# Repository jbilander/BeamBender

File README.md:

# BeamBender
An open source flicker fixer PCB for Amiga 1200 and 500 to be fitted under the floppy drive.

WORK IN PROGRESS, NOT FINISHED!!!

***

Rev. 1B
<br />

<br />

***

Rev. 1A
<br />

<br />

<br />

<br />

<br />

<br />

<br />

***

BOM Rev. 1B
---------
Designator  | Name/Value   | Package | Notes
-|-|-|-|
U1 | Voltage Regulator 3.3V, <br /> LM1117-3.3 or <br /> AMS1117-3.3 | SOT-223 | 3.3V 1A Low Drop-Out (LDO) Voltage regulator. https://www.aliexpress.com/item/32869037691.html
U2 | Gowin FPGA GW1NR-UV9LQ144PC6/I5 | LQFP-144 | FPGA - Field Programmable Gate Array, 8640 LE, 121 I/O, Embedded 64Mbit 16-bit PSRAM <br /> [GW1NR-UV9LQ144PC6/I5](https://www.mouser.com/ProductDetail/192-1NRUV9LQ144PC6I5)
U3 | SiI9022A | QFN-72-1EP_10x10mm_P0.5mm_EP4.7x4.7mm | 165 MHz High Performance HDMI Transmitter [SII9022ACNU](https://www.mouser.com/ProductDetail/842-SII9022ACNU)
U4 | Voltage Regulator 1.8V, <br /> MCP1702T-1802E/CB | SOT-23 | 1.8V Low Drop-Out (LDO) Voltage regulator. [MCP1702T1802E-CB](https://www.mouser.com/ProductDetail/579-MCP1702T1802E-CB)
U5 | Audio A/D Converter AK5720VT | TSSOP-16 | ADC IC 2ch 24bit 96K. [AK5720VT](https://www.mouser.se/ProductDetail/412-AK5720VT)
U6 | Voltage Regulator 1.2V, <br /> MCP1702T-1202E/CB | SOT-23 | 1.2V Low Drop-Out (LDO) Voltage regulator. [MCP1702T1202E-CB](https://eu.mouser.com/ProductDetail/579-MCP1702T1202E-CB)
X1 | Abracon ASE-27.000MHZ-L-R-T | XTAL OSC SMD 3.2 mm x 2.5 mm | Standard Clock Oscillator XO 27MHZ CMOS SMD [ASE-27.000MHZ-L-R-T](https://www.mouser.com/ProductDetail/815-ASE-27.000-LR-T)
X2 | Abracon ASFL1-24.576MHZ-EC-T | XTAL OSC SMD 5.0 mm x 3.2 mm | Standard Clock Oscillators 24.576 MHZ 15PF 3.3V [ASFL1-24.576MHZ-EC-T](https://www.mouser.com/ProductDetail/815-ASFL1-24.5-EC-T)
X3 | Standard Clock Oscillator 50 MHz, 3.3V LVCMOS | XTAL OSC SMD 7 mm x 5 mm | e.g. [FN5000109](https://www.mouser.com/ProductDetail/729-FN5000109) or [LH736050](https://www.mouser.com/ProductDetail/972-LH736050.000000I)
J1 | FFC & FPC Connectors .5 FPC VT ZIF Type-A | 40 Position FPC connector, Pitch 0.5 mm | [TE Connectivity 4-1734742-0](https://www.mouser.com/ProductDetail/571-4-1734742-0)
J2 | HDMI 1.4 Receptacle Connector 19 Position Surface Mount, Right Angle TH | HDMI Receptacle | [Amphenol 10029449-111RLF](https://www.mouser.com/ProductDetail/649-10029449-111RLF)
J3 | Phone Connectors 3.5 mm, Stereo | 3 Position Through Hole | [Kycon STX-3501-3N](https://www.mouser.com/ProductDetail/806-STX-3501-3N)
J4 | VCC/GND Phoenix Contact 2pin 2.54mm pitch | Fixed Terminal Blocks 2P 2.54mm 90DEG | VIN +5V <br /> Be careful with orientation, check polarity BEFORE connecting anything here. You can take +5V/GND from internal floppy pin-header on Amiga motherboard.<br />[1725656](https://www.mouser.com/ProductDetail/651-1725656) or [Aliexpress](https://www.aliexpress.com/item/1005001677869988.html)
D1-D3 | ESD Suppressors / TVS Diodes | U-DFN2510-10 | [D5V0F4U10LP-7](https://www.mouser.com/ProductDetail/621-D5V0F4U10LP-7)
D4 | ESD Suppressor / TVS Diode 1 Ch | SOD-723-2 | [SP1003-01DTG](https://www.mouser.com/ProductDetail/576-SP1003-01DTG) Optional ESD protection for VCC.
D5 | Diode - General Purpose | 0805 | e.g. [TS4148RBG](https://www.mouser.com/ProductDetail/821-TS4148RBG) Diode in RC-debounce (R5, C34) circuit for BT1 (Button 1).
L1-L4 | Ferrite Bead 600ohms 100MHz .5A Monolithic | 0805 | e.g. [HZ0805E601R-10](https://www.mouser.com/ProductDetail/875-HZ0805E601R-10)
C1-C13 | Capacitor 10uF | 1206 |
C14 | Capacitor 0.47uF | 1206 | e.g. [UMK316B7474KL-T](https://www.mouser.com/ProductDetail/963-UMK316B7474KL-T)
C15, C16 | Capacitor 0.1uF | 1206 |
C17 | Polarized Capacitor 100uF | CP_Elec_6.3x7.7 | e.g. [Wurth SMD WCAP-AS5H 100uF](https://www.mouser.com/ProductDetail/710-865230245004)
C18, C19 | Polarized Capacitor 22uF | CP_Elec_5x5.8 | e.g. [Wurth SMD WCAP-AS5H 22uF](https://www.mouser.com/ProductDetail/710-865230342002)
C20-C22 | Capacitor 1uF | 0805 |
C23-C43 | Capacitor 0.1uF = 100nF | 0805 |
C44-C47 | Capacitor 0.1uF = 100nF | 0603 |
C48-C53 | Capacitor 0.01uF = 10nF | 0603 |
R1-R3 | 1k Ω | 0805 |
R4, R5 | 10k Ω | 0805 |
R6 | 0-9 Ω or solder blob| 0805 | e.g. [CR0805-J/-000ELF](https://www.mouser.com/ProductDetail/652-CR0805-J-000ELF)
R7-R14 | 33 Ω | 0603 | e.g. [CR0603-FX-33R0ELF](https://www.mouser.com/ProductDetail/652-CR0603FX-33R0ELF)
R15, R16 | 2k Ω | 0603 | e.g. [CR0603-FX-2001ELF](https://www.mouser.com/ProductDetail/652-CR0603-FX-2001LF)
R17 | 4.3k Ω, 1% tolerance | 0603 | e.g. [CR0603-FX-4301ELF](https://www.mouser.com/ProductDetail/652-CR0603FX-4301ELF) The recommended value is 4.3k Ω ±1% with internal source termination enabled and 5.1k Ω ±1% without internal source termination. 
R18-R20 | 4.7k Ω | 0603 | 
R21 | 10k Ω | 0603 |
RN1, RN2 | CAY16A-4701F4LF RES ARRAY 4 Resistors 4.7k Ω | 1206 | [CAY16A-4701F4LF](https://eu.mouser.com/ProductDetail/652-CAY16A-4701F4LF)

***

[![CC BY-SA 4.0][cc-by-sa-shield]][cc-by-sa]

This work is licensed under a
[Creative Commons Attribution-ShareAlike 4.0 International License][cc-by-sa].

[![CC BY-SA 4.0][cc-by-sa-image]][cc-by-sa]

[cc-by-sa]: http://creativecommons.org/licenses/by-sa/4.0/
[cc-by-sa-image]: https://licensebuttons.net/l/by-sa/4.0/88x31.png
[cc-by-sa-shield]: https://img.shields.io/badge/License-CC%20BY--SA%204.0-lightgrey.svg

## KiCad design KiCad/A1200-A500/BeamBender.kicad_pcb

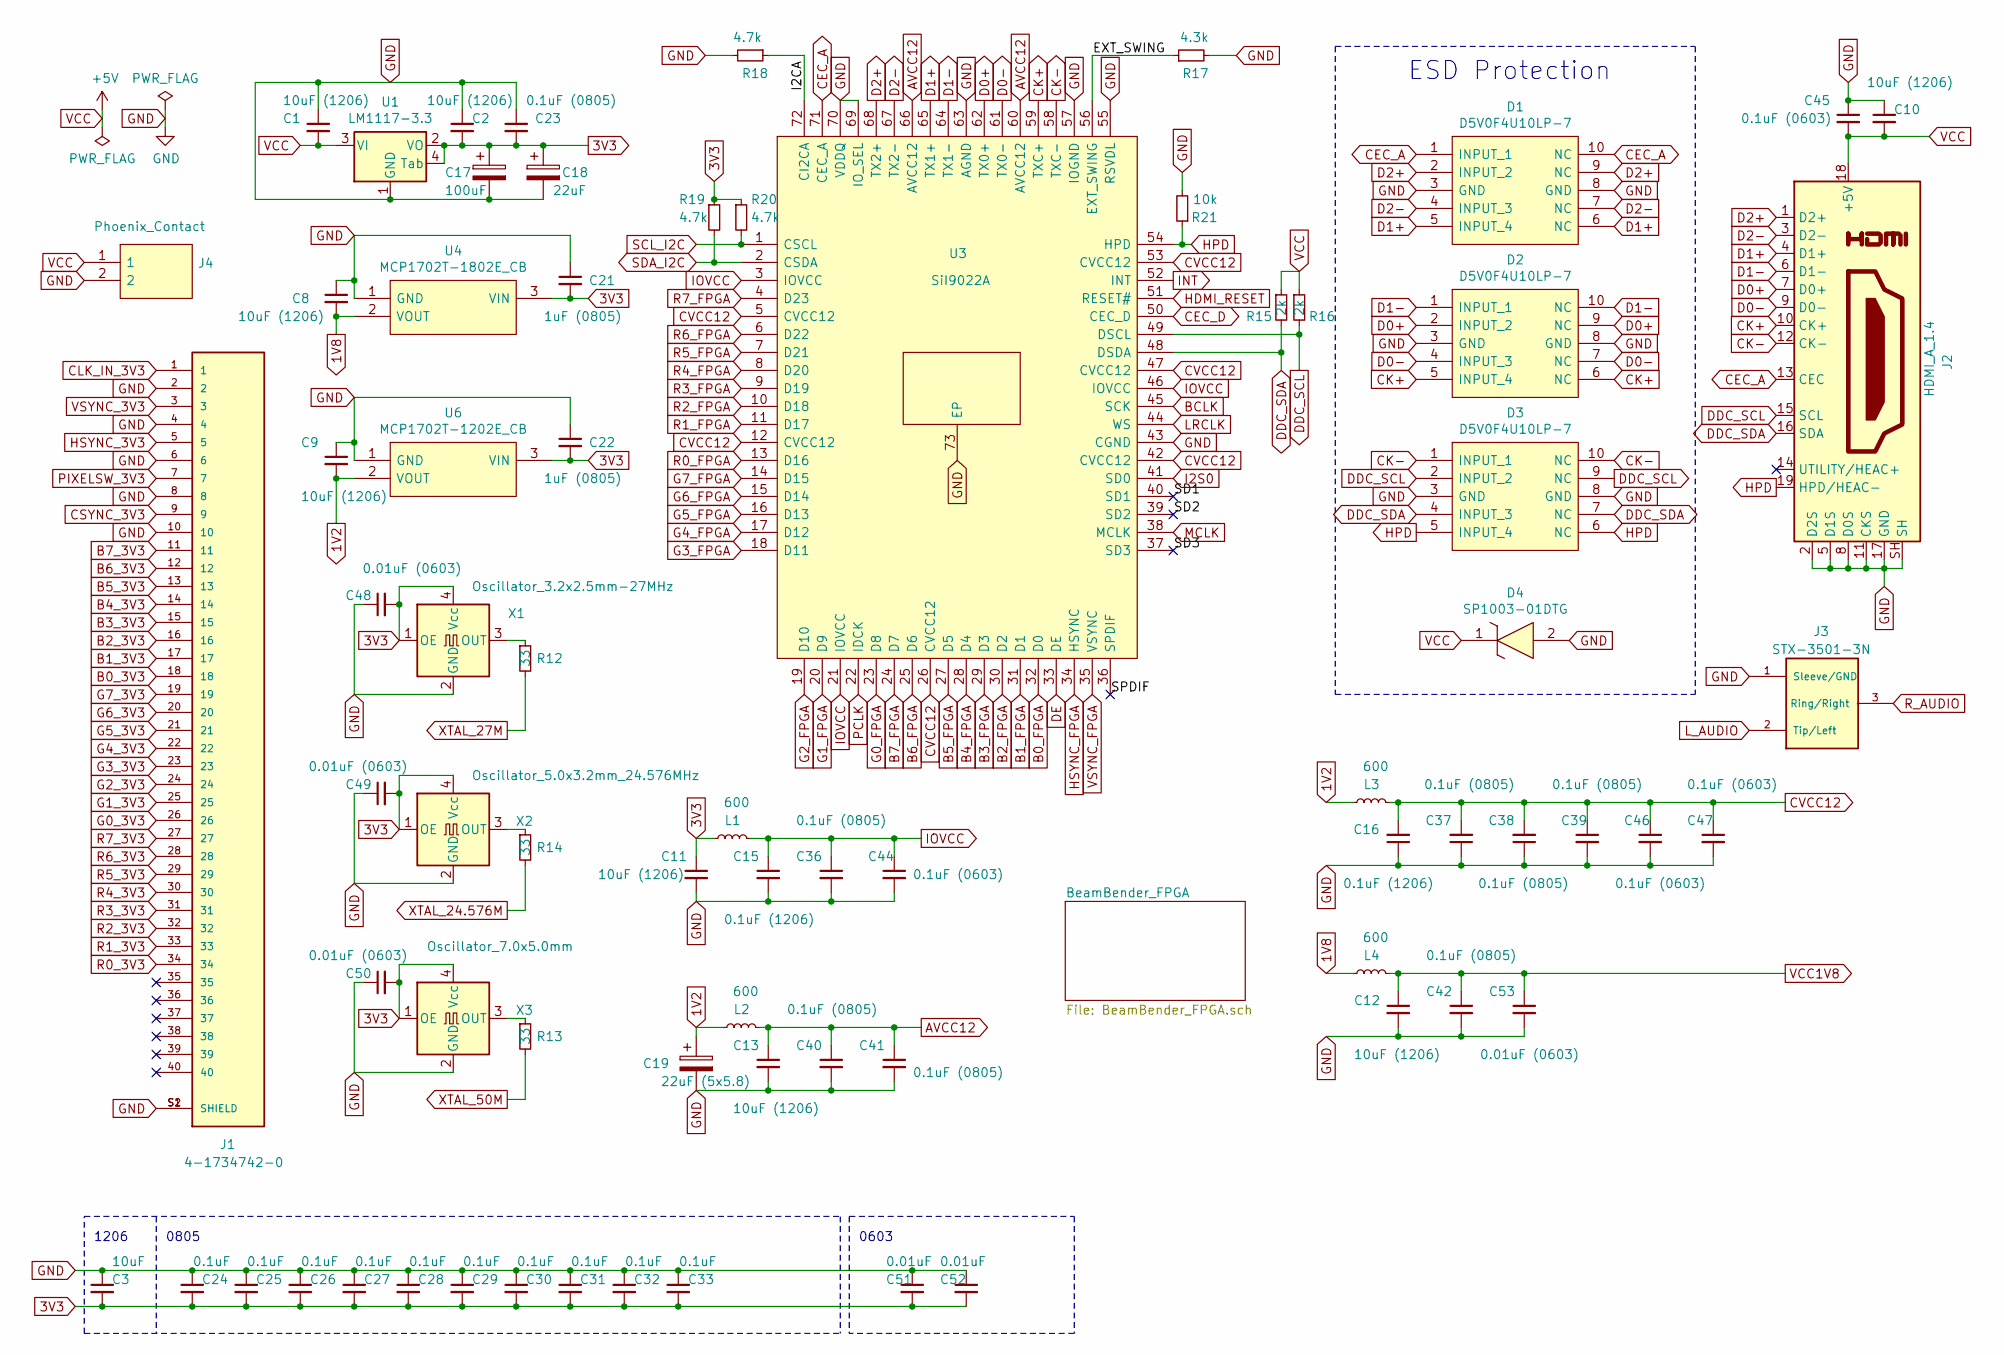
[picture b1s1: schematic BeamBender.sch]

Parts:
C1, C2: 10uF (1206); C_1206_3216Metric_Pad1.42x1.75mm_HandSolder
C3: 10uF; C_1206_3216Metric_Pad1.33x1.80mm_HandSolder
C8, C9, C10, C11, C12, C13: 10uF (1206); C_1206_3216Metric_Pad1.33x1.80mm_HandSolder
C15, C16: 0.1uF (1206); C_1206_3216Metric_Pad1.33x1.80mm_HandSolder
C17: 100uF; CP_Elec_6.3x7.7
C18: 22uF; CP_Elec_5x5.8
C19: 22uF (5x5.8); CP_Elec_5x5.8
C21, C22: 1uF (0805); C_0805_2012Metric_Pad1.18x1.45mm_HandSolder
C23: 0.1uF (0805); C_0805_2012Metric_Pad1.15x1.40mm_HandSolder
C24, C25, C26, C27, C28, C29, C30, C31, C32, C33: 0.1uF; C_0805_2012Metric_Pad1.18x1.45mm_HandSolder
C36, C37, C38, C39, C40, C41, C42: 0.1uF (0805); C_0805_2012Metric_Pad1.18x1.45mm_HandSolder
C44, C45, C46, C47: 0.1uF (0603); C_0603_1608Metric_Pad1.08x0.95mm_HandSolder
C48, C49, C50, C53: 0.01uF (0603); C_0603_1608Metric_Pad1.08x0.95mm_HandSolder
C51, C52: 0.01uF; C_0603_1608Metric_Pad1.08x0.95mm_HandSolder
D1, D2, D3: D5V0F4U10LP-7; Diodes_UDFN-10_1.0x2.5mm_P0.5mm_HandSolder
D4: SP1003-01DTG; D_0603_1608Metric
J1: 4-1734742-0; TE_4-1734742-0; PARTREV P
J2: HDMI_A_1.4; HDMI-10029449-111RLF
J3: STX-3501-3N; STX35013N
J4: Phoenix_Contact
L1, L2, L3, L4: 600; L_0805_2012Metric_Pad1.15x1.40mm_HandSolder
R12, R13, R14: 33; R_0603_1608Metric_Pad0.98x0.95mm_HandSolder
R15, R16: 2k; R_0603_1608Metric_Pad0.98x0.95mm_HandSolder
R17: 4.3k; R_0603_1608Metric_Pad0.98x0.95mm_HandSolder
R18, R19, R20: 4.7k; R_0603_1608Metric_Pad0.98x0.95mm_HandSolder
R21: 10k; R_0603_1608Metric_Pad0.98x0.95mm_HandSolder
U1: LM1117-3.3; SOT-223
U3: SiI9022A; QFN-72-1EP_10x10mm_P0.5mm_EP6x6mm_ThermalVias_HandSolder
U4: MCP1702T-1802E_CB; SOT-23_Handsoldering
U6: MCP1702T-1202E_CB; SOT-23_Handsoldering
X1: Oscillator_3.2x2.5mm-27MHz; Oscillator_SMD_SeikoEpson_SG8002CE-4Pin_3.2x2.5mm
X2: Oscillator_5.0x3.2mm_24.576MHz; Oscillator_SMD_TXC_7C-4Pin_5.0x3.2mm_HandSoldering
X3: Oscillator_7.0x5.0mm; Oscillator_SMD_SeikoEpson_SG8002CA-4Pin_7.0x5.0mm_HandSolde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

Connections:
1V2: C9.2, C19.1, L2.1, L3.1, U6.2 (VOUT)
1V8: C8.2, L4.1, U4.2 (VOUT)
3V3: C2.2, C3.2, C11.1, C17.1, C18.1, C21.2, C22.2, C23.2, C24.2, C25.2, C26.2, C27.2, C28.2, C29.2, C30.2, C31.2, C32.2, C33.2, C48.2, C49.2, C50.2, C51.2, C52.2, L1.1, R19.1, R20.1, U1.2 (VO), U1.4 (Tab), U4.3 (VIN), U6.3 (VIN), X1.1 (OE), X1.4 (Vcc), X2.1 (OE), X2.4 (Vcc), X3.1 (OE), X3.4 (Vcc); also elsewhere on the board
/EXT_SWING: R17.1, U3.56 (EXT_SWING)
/I2CA: R18.1, U3.72 (CI2CA)
/SD1: U3.40 (SD1)
/SD2: U3.39 (SD2)
/SD3: U3.37 (SD3)
/SPDIF: U3.36 (SPDIF)
AVCC12: C13.1, C40.1, C41.1, L2.2, U3.60 (AVCC12), U3.66 (AVCC12)
B0_3V3: J1.18; also elsewhere on the board
B0_FPGA: U3.32 (D0); also elsewhere on the board
B1_3V3: J1.17; also elsewhere on the board
B1_FPGA: U3.31 (D1); also elsewhere on the board
B2_3V3: J1.16; also elsewhere on the board
B2_FPGA: U3.30 (D2); also elsewhere on the board
B3_3V3: J1.15; also elsewhere on the board
B3_FPGA: U3.29 (D3); also elsewhere on the board
B4_3V3: J1.14; also elsewhere on the board
B4_FPGA: U3.28 (D4); also elsewhere on the board
B5_3V3: J1.13; also elsewhere on the board
B5_FPGA: U3.27 (D5); also elsewhere on the board
B6_3V3: J1.12; also elsewhere on the board
B6_FPGA: U3.25 (D6); also elsewhere on the board
B7_3V3: J1.11; also elsewhere on the board
B7_FPGA: U3.24 (D7); also elsewhere on the board
BCLK: U3.45 (SCK); also elsewhere on the board
CEC_A: D1.1 (INPUT_1), D1.10 (NC), J2.13 (CEC), U3.71 (CEC_A)
CEC_D: U3.50 (CEC_D); also elsewhere on the board
CK+: D2.5 (INPUT_4), D2.6 (NC), J2.10 (CK+), U3.59 (TXC+)
CK-: D3.1 (INPUT_1), D3.10 (NC), J2.12 (CK-), U3.58 (TXC-)
CLK_IN_3V3: J1.1; also elsewhere on the board
CSYNC_3V3: J1.9; also elsewhere on the board
CVCC12: C16.2, C37.2, C38.2, C39.1, C46.1, C47.1, L3.2, U3.5 (CVCC12), U3.12 (CVCC12), U3.26 (CVCC12), U3.42 (CVCC12), U3.47 (CVCC12), U3.53 (CVCC12)
D0+: D2.2 (INPUT_2), D2.9 (NC), J2.7 (D0+), U3.62 (TX0+)
D0-: D2.4 (INPUT_3), D2.7 (NC), J2.9 (D0-), U3.61 (TX0-)
D1+: D1.5 (INPUT_4), D1.6 (NC), J2.4 (D1+), U3.65 (TX1+)
D1-: D2.1 (INPUT_1), D2.10 (NC), J2.6 (D1-), U3.64 (TX1-)
D2+: D1.2 (INPUT_2), D1.9 (NC), J2.1 (D2+), U3.68 (TX2+)
D2-: D1.4 (INPUT_3), D1.7 (NC), J2.3 (D2-), U3.67 (TX2-)
DDC_SCL: D3.2 (INPUT_2), D3.9 (NC), J2.15 (SCL), R16.2, U3.49 (DSCL)
DDC_SDA: D3.4 (INPUT_3), D3.7 (NC), J2.16 (SDA), R15.2, U3.48 (DSDA)
DE: U3.33 (DE); also elsewhere on the board
G0_3V3: J1.26; also elsewhere on the board
G0_FPGA: U3.23 (D8); also elsewhere on the board
G1_3V3: J1.25; also elsewhere on the board
G1_FPGA: U3.20 (D9); also elsewhere on the board
G2_3V3: J1.24; also elsewhere on the board
G2_FPGA: U3.19 (D10); also elsewhere on the board
G3_3V3: J1.23; also elsewhere on the board
G3_FPGA: U3.18 (D11); also elsewhere on the board
G4_3V3: J1.22; also elsewhere on the board
G4_FPGA: U3.17 (D12); also elsewhere on the board
G5_3V3: J1.21; also elsewhere on the board
G5_FPGA: U3.16 (D13); also elsewhere on the board
G6_3V3: J1.20; also elsewhere on the board
G6_FPGA: U3.15 (D14); also elsewhere on the board
G7_3V3: J1.19; also elsewhere on the board
G7_FPGA: U3.14 (D15); also elsewhere on the board
GND: C1.1, C2.1, C3.1, C8.1, C9.1, C10.1, C11.2, C12.2, C13.2, C15.2, C16.1, C17.2, C18.2, C19.2, C21.1, C22.1, C23.1, C24.1, C25.1, C26.1, C27.1, C28.1, C29.1, C30.1, C31.1, C32.1, C33.1, C36.2, C37.1, C38.1, C39.2, C40.2, C41.2, C42.2, C44.2, C45.1, C46.2, C47.2, C48.1, C49.1, C50.1, C51.1, C52.1, C53.2, D1.3 (GND), D1.8 (GND), D2.3 (GND), D2.8 (GND), D3.3 (GND), D3.8 (GND), D4.2, J1.2, J1.4, J1.6, J1.8, J1.10, J1.S1 (SHIELD), J1.S2 (SHIELD), J2.2 (D2S), J2.5 (D1S), J2.8 (D0S), J2.11 (CKS), J2.17 (GND), J2.SH, J3.1 (Sleeve/GND), J4.2, R17.2, R18.2, R21.2, U1.1 (GND), U3.43 (CGND), U3.55 (RSVDL), U3.57 (IOGND), U3.63 (AGND), U3.69 (IO_SEL), U3.70 (VDDQ), U3.73 (EP), U4.1 (GND), U6.1 (GND), X1.2 (GND), X2.2 (GND), X3.2 (GND); also elsewhere on the board
HDMI_RESET: U3.51 (RESET#); also elsewhere on the board
HPD: D3.5 (INPUT_4), D3.6 (NC), J2.19 (HPD/HEAC-), R21.1, U3.54 (HPD)
HSYNC_3V3: J1.5; also elsewhere on the board
HSYNC_FPGA: U3.34 (HSYNC); also elsewhere on the board
I2S0: U3.41 (SD0); also elsewhere on the board
INT: U3.52 (INT); also elsewhere on the board
IOVCC: C15.1, C36.1, C44.1, L1.2, U3.3 (IOVCC), U3.21 (IOVCC), U3.46 (IOVCC)
LRCLK: U3.44 (WS); also elsewhere on the board
L_AUDIO: J3.2 (Tip/Left); also elsewhere on the board
MCLK: U3.38 (MCLK); also elsewhere on the board
unnamed: R12.1, X1.3 (OUT)
unnamed: R13.1, X3.3 (OUT)
unnamed: R14.1, X2.3 (OUT)
PCLK: U3.22 (IDCK); also elsewhere on the board
PIXELSW_3V3: J1.7; also elsewhere on the board
R0_3V3: J1.34; also elsewhere on the board
R0_FPGA: U3.13 (D16); also elsewhere on the board
R1_3V3: J1.33; also elsewhere on the board
R1_FPGA: U3.11 (D17); also elsewhere on the board
R2_3V3: J1.32; also elsewhere on the board
R2_FPGA: U3.10 (D18); also elsewhere on the board
R3_3V3: J1.31; also elsewhere on the board
R3_FPGA: U3.9 (D19); also elsewhere on the board
R4_3V3: J1.30; also elsewhere on the board
R4_FPGA: U3.8 (D20); also elsewhere on the board
R5_3V3: J1.29; also elsewhere on the board
R5_FPGA: U3.7 (D21); also elsewhere on the board
R6_3V3: J1.28; also elsewhere on the board
R6_FPGA: U3.6 (D22); also elsewhere on the board
R7_3V3: J1.27; also elsewhere on the board
R7_FPGA: U3.4 (D23); also elsewhere on the board
R_AUDIO: J3.3 (Ring/Right); also elsewhere on the board
SCL_I2C: R20.2, U3.1 (CSCL); also elsewhere on the board
SDA_I2C: R19.2, U3.2 (CSDA); also elsewhere on the board
VCC: C1.2, C10.2, C45.2, D4.1, J2.18 (+5V), J4.1, R15.1, R16.1, U1.3 (VI); also elsewhere on the board
VCC1V8: C12.1, C42.1, C53.1, L4.2; also elsewhere on the board
VSYNC_3V3: J1.3; also elsewhere on the board
VSYNC_FPGA: U3.35 (VSYNC); also elsewhere on the board
XTAL_24.576M: R14.2; also elsewhere on the board
XTAL_27M: R12.2; also elsewhere on the board
XTAL_50M: R13.2; also elsewhere on the board

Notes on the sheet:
ESD Protection
0805
0603
1206

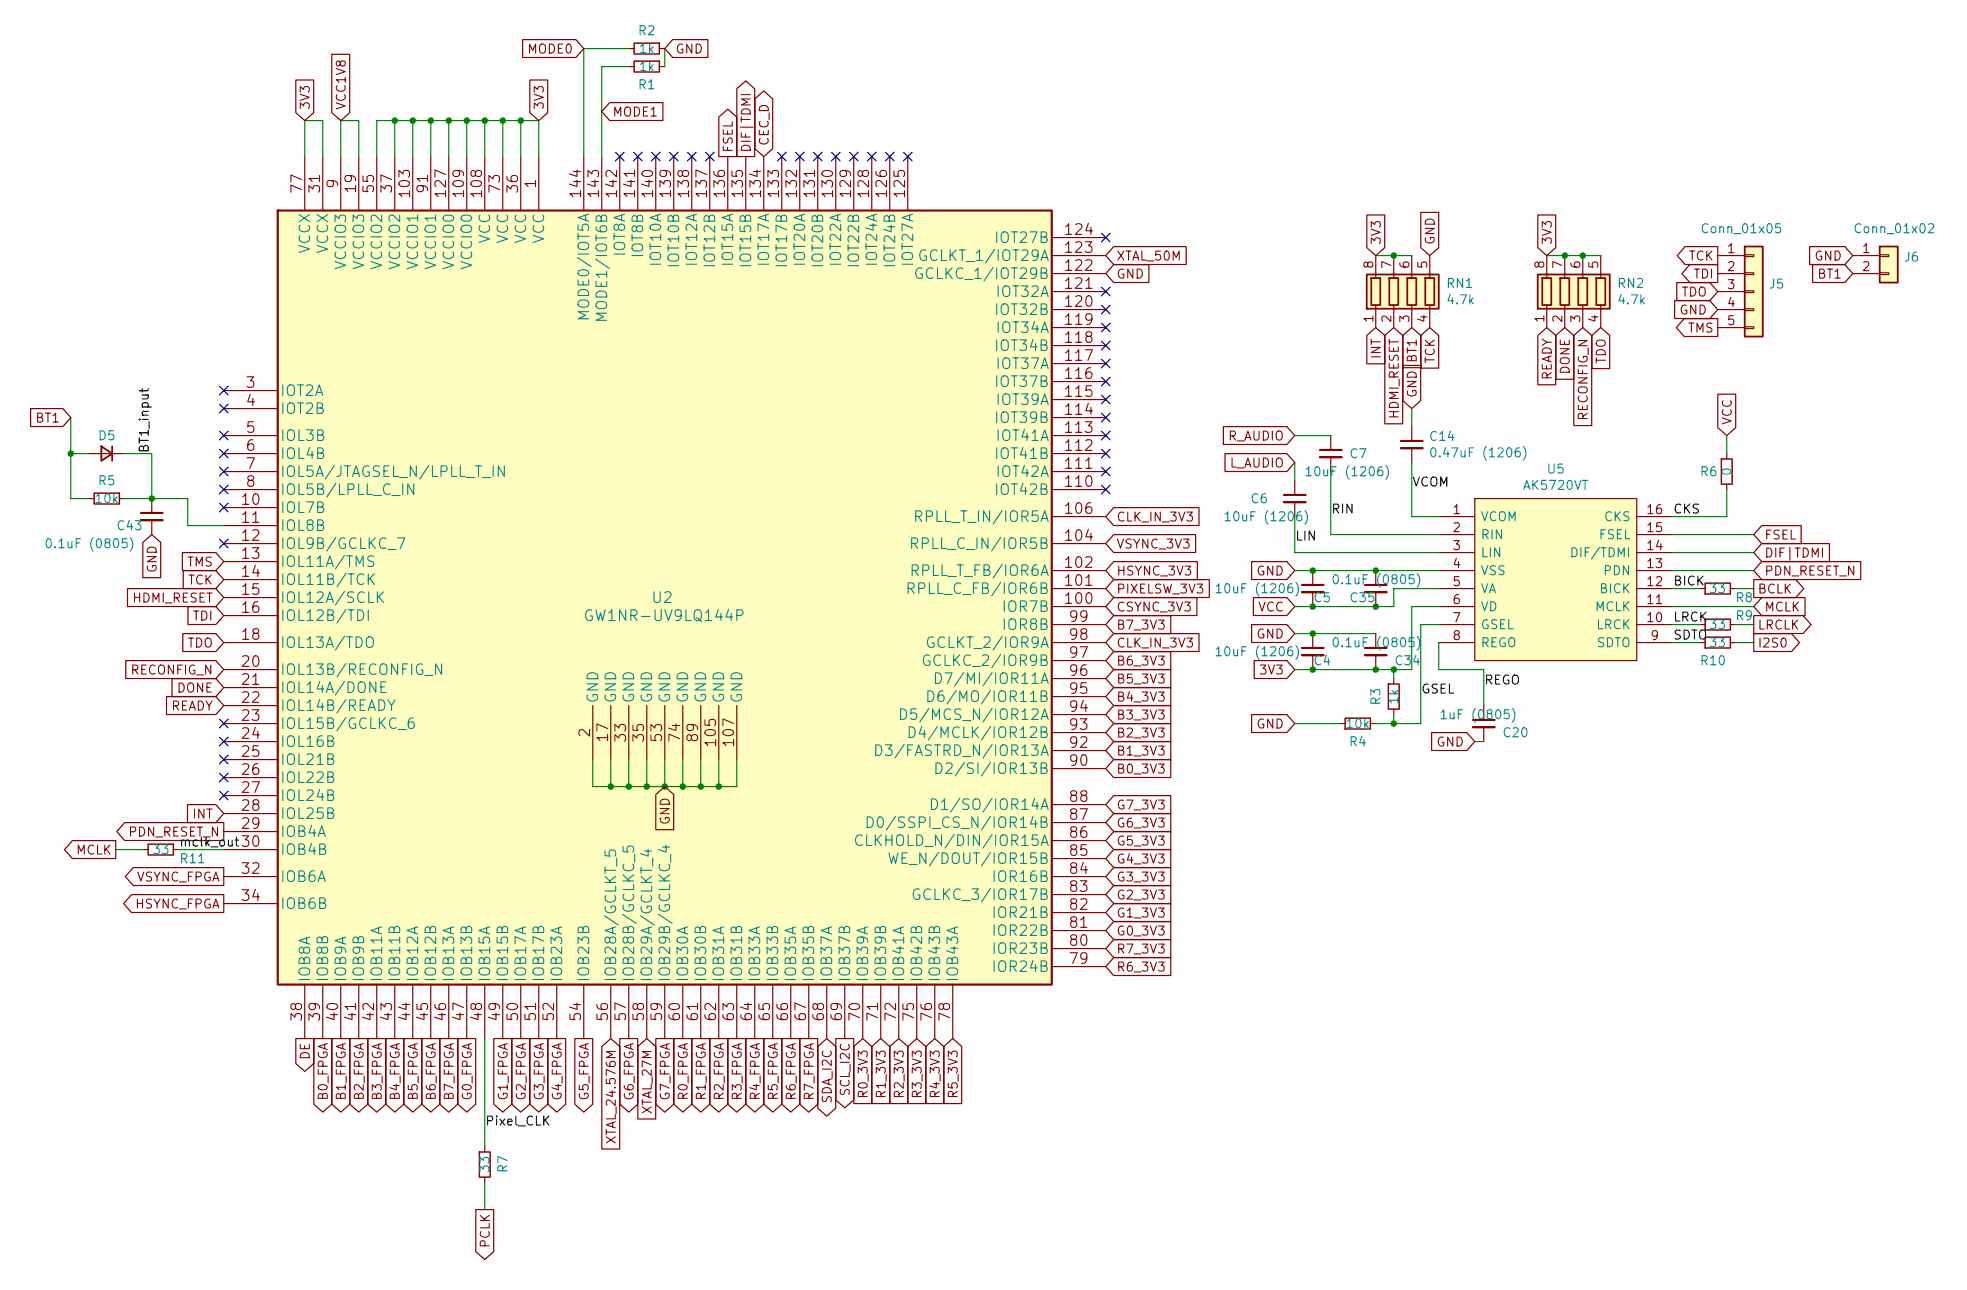
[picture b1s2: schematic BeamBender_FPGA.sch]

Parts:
C4, C5, C6, C7: 10uF (1206); C_1206_3216Metric_Pad1.33x1.80mm_HandSolder
C14: 0.47uF (1206); C_1206_3216Metric_Pad1.33x1.80mm_HandSolder
C20: 1uF (0805); C_0805_2012Metric_Pad1.18x1.45mm_HandSolder
C34, C35, C43: 0.1uF (0805); C_0805_2012Metric_Pad1.18x1.45mm_HandSolder
D5: D_Small; D_0805_2012Metric_Pad1.15x1.40mm_HandSolder
J5: Conn_01x05; PinHeader_1x05_P2.54mm_Vertical
J6: Conn_01x02; PinHeader_1x02_P2.54mm_Vertical
R1, R2, R3: 1k; R_0805_2012Metric_Pad1.20x1.40mm_HandSolder
R4, R5: 10k; R_0805_2012Metric_Pad1.20x1.40mm_HandSolder
R6: 0; R_0805_2012Metric_Pad1.20x1.40mm_HandSolder
R7, R8, R9, R10, R11: 33; R_0603_1608Metric_Pad0.98x0.95mm_HandSolder
RN1, RN2: 4.7k; RESCAF80P320X160X60-8N
U2: GW1NR-UV9LQ144P; LQFP-144_20x20mm_P0.5mm
U5: AK5720VT; TSSOP-16_4.4x5mm_P0.65mm

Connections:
3V3: C4.2, C34.2, R3.1, RN1.6 (R3.2), RN1.7 (R2.2), RN1.8 (R1.2), RN2.5 (R4.2), RN2.6 (R3.2), RN2.7 (R2.2), RN2.8 (R1.2), U2.1 (VCC), U2.31 (VCCX), U2.36 (VCC), U2.37 (VCCIO2), U2.55 (VCCIO2), U2.73 (VCC), U2.77 (VCCX), U2.91 (VCCIO1), U2.103 (VCCIO1), U2.108 (VCC), U2.109 (VCCIO0), U2.127 (VCCIO0), U5.6 (VD); also elsewhere on the board
/BeamBender_FPGA/BICK: R8.1, U5.12 (BICK)
/BeamBender_FPGA/BT1_input: C43.1, D5.1 (K), R5.1, U2.11 (IOL8B)
/BeamBender_FPGA/CKS: R6.2, U5.16 (CKS)
/BeamBender_FPGA/GSEL: R3.2, R4.2, U5.7 (GSEL)
/BeamBender_FPGA/LIN: C6.2, U5.3 (LIN)
/BeamBender_FPGA/LRCK: R9.1, U5.10 (LRCK)
/BeamBender_FPGA/Pixel_CLK: R7.1, U2.48 (IOB15A)
/BeamBender_FPGA/REGO: C20.1, U5.8 (REGO)
/BeamBender_FPGA/RIN: C7.2, U5.2 (RIN)
/BeamBender_FPGA/SDTO: R10.1, U5.9 (SDTO)
/BeamBender_FPGA/VCOM: C14.2, U5.1 (VCOM)
/BeamBender_FPGA/mclk_out: R11.1, U2.30 (IOB4B)
B0_3V3: U2.90 (D2/SI/IOR13B); also elsewhere on the board
B0_FPGA: U2.39 (IOB8B); also elsewhere on the board
B1_3V3: U2.92 (D3/FASTRD_N/IOR13A); also elsewhere on the board
B1_FPGA: U2.40 (IOB9A); also elsewhere on the board
B2_3V3: U2.93 (D4/MCLK/IOR12B); also elsewhere on the board
B2_FPGA: U2.41 (IOB9B); also elsewhere on the board
B3_3V3: U2.94 (D5/MCS_N/IOR12A); also elsewhere on the board
B3_FPGA: U2.42 (IOB11A); also elsewhere on the board
B4_3V3: U2.95 (D6/MO/IOR11B); also elsewhere on the board
B4_FPGA: U2.43 (IOB11B); also elsewhere on the board
B5_3V3: U2.96 (D7/MI/IOR11A); also elsewhere on the board
B5_FPGA: U2.44 (IOB12A); also elsewhere on the board
B6_3V3: U2.97 (GCLKC_2/IOR9B); also elsewhere on the board
B6_FPGA: U2.45 (IOB12B); also elsewhere on the board
B7_3V3: U2.99 (IOR8B); also elsewhere on the board
B7_FPGA: U2.46 (IOB13A); also elsewhere on the board
BCLK: R8.2; also elsewhere on the board
BT1: D5.2 (A), J6.2, R5.2, RN1.3 (R3.1)
CEC_D: U2.134 (IOT17A); also elsewhere on the board
CLK_IN_3V3: U2.98 (GCLKT_2/IOR9A), U2.106 (RPLL_T_IN/IOR5A); also elsewhere on the board
CSYNC_3V3: U2.100 (IOR7B); also elsewhere on the board
DE: U2.38 (IOB8A); also elsewhere on the board
DIF|TDMI: U2.135 (IOT15B), U5.14 (DIF/TDMI)
DONE: RN2.2 (R2.1), U2.21 (IOL14A/DONE)
FSEL: U2.136 (IOT15A), U5.15 (FSEL)
G0_3V3: U2.81 (IOR22B); also elsewhere on the board
G0_FPGA: U2.47 (IOB13B); also elsewhere on the board
G1_3V3: U2.82 (IOR21B); also elsewhere on the board
G1_FPGA: U2.49 (IOB15B); also elsewhere on the board
G2_3V3: U2.83 (GCLKC_3/IOR17B); also elsewhere on the board
G2_FPGA: U2.50 (IOB17A); also elsewhere on the board
G3_3V3: U2.84 (IOR16B); also elsewhere on the board
G3_FPGA: U2.51 (IOB17B); also elsewhere on the board
G4_3V3: U2.85 (WE_N/DOUT/IOR15B); also elsewhere on the board
G4_FPGA: U2.52 (IOB23A); also elsewhere on the board
G5_3V3: U2.86 (CLKHOLD_N/DIN/IOR15A); also elsewhere on the board
G5_FPGA: U2.54 (IOB23B); also elsewhere on the board
G6_3V3: U2.87 (D0/SSPI_CS_N/IOR14B); also elsewhere on the board
G6_FPGA: U2.57 (IOB28B/GCLKC_5); also elsewhere on the board
G7_3V3: U2.88 (D1/SO/IOR14A); also elsewhere on the board
G7_FPGA: U2.59 (IOB29B/GCLKC_4); also elsewhere on the board
GND: C4.1, C5.1, C14.1, C20.2, C34.1, C35.1, C43.2, J5.4, J6.1, R1.1, R2.1, R4.1, RN1.5 (R4.2), U2.2 (GND), U2.17 (GND), U2.33 (GND), U2.35 (GND), U2.53 (GND), U2.74 (GND), U2.89 (GND), U2.105 (GND), U2.107 (GND), U2.122 (GCLKC_1/IOT29B), U5.4 (VSS); also elsewhere on the board
HDMI_RESET: RN1.2 (R2.1), U2.15 (IOL12A/SCLK); also elsewhere on the board
HSYNC_3V3: U2.102 (RPLL_T_FB/IOR6A); also elsewhere on the board
HSYNC_FPGA: U2.34 (IOB6B); also elsewhere on the board
I2S0: R10.2; also elsewhere on the board
INT: RN1.1 (R1.1), U2.28 (IOL25B); also elsewhere on the board
LRCLK: R9.2; also elsewhere on the board
L_AUDIO: C6.1; also elsewhere on the board
MCLK: R11.2, U5.11 (MCLK); also elsewhere on the board
MODE0: R2.2, U2.144 (MODE0/IOT5A)
MODE1: R1.2, U2.143 (MODE1/IOT6B)
PCLK: R7.2; also elsewhere on the board
PDN_RESET_N: U2.29 (IOB4A), U5.13 (PDN)
PIXELSW_3V3: U2.101 (RPLL_C_FB/IOR6B); also elsewhere on the board
R0_3V3: U2.70 (IOB39A); also elsewhere on the board
R0_FPGA: U2.60 (IOB30A); also elsewhere on the board
R1_3V3: U2.71 (IOB39B); also elsewhere on the board
R1_FPGA: U2.61 (IOB30B); also elsewhere on the board
R2_3V3: U2.72 (IOB41A); also elsewhere on the board
R2_FPGA: U2.62 (IOB31A); also elsewhere on the board
R3_3V3: U2.75 (IOB42B); also elsewhere on the board
R3_FPGA: U2.63 (IOB31B); also elsewhere on the board
R4_3V3: U2.76 (IOB43B); also elsewhere on the board
R4_FPGA: U2.64 (IOB33A); also elsewhere on the board
R5_3V3: U2.78 (IOB43A); also elsewhere on the board
R5_FPGA: U2.65 (IOB33B); also elsewhere on the board
R6_3V3: U2.79 (IOR24B); also elsewhere on the board
R6_FPGA: U2.66 (IOB35A); also elsewhere on the board
R7_3V3: U2.80 (IOR23B); also elsewhere on the board
R7_FPGA: U2.67 (IOB35B); also elsewhere on the board
READY: RN2.1 (R1.1), U2.22 (IOL14B/READY)
RECONFIG_N: RN2.3 (R3.1), U2.20 (IOL13B/RECONFIG_N)
R_AUDIO: C7.1; also elsewhere on the board
SCL_I2C: U2.69 (IOB37B); also elsewhere on the board
SDA_I2C: U2.68 (IOB37A); also elsewhere on the board
TCK: J5.1, RN1.4 (R4.1), U2.14 (IOL11B/TCK)
TDI: J5.2, U2.16 (IOL12B/TDI)
TDO: J5.3, RN2.4 (R4.1), U2.18 (IOL13A/TDO)
TMS: J5.5, U2.13 (IOL11A/TMS)
VCC: C5.2, C35.2, R6.1, U5.5 (VA); also elsewhere on the board
VCC1V8: U2.9 (VCCIO3), U2.19 (VCCIO3); also elsewhere on the board
VSYNC_3V3: U2.104 (RPLL_C_IN/IOR5B); also elsewhere on the board
VSYNC_FPGA: U2.32 (IOB6A); also elsewhere on the board
XTAL_24.576M: U2.56 (IOB28A/GCLKT_5); also elsewhere on the board
XTAL_27M: U2.58 (IOB29A/GCLKT_4); also elsewhere on the board
XTAL_50M: U2.123 (GCLKT_1/IOT29A); also elsewhere on the board

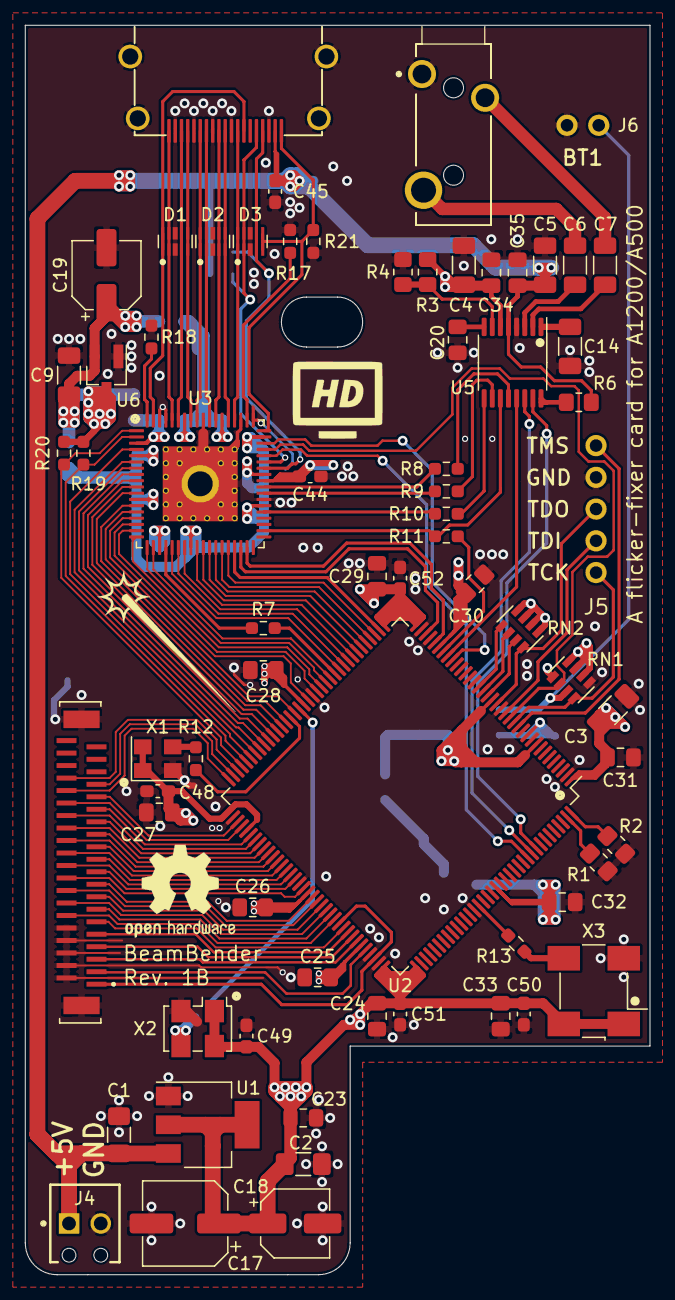
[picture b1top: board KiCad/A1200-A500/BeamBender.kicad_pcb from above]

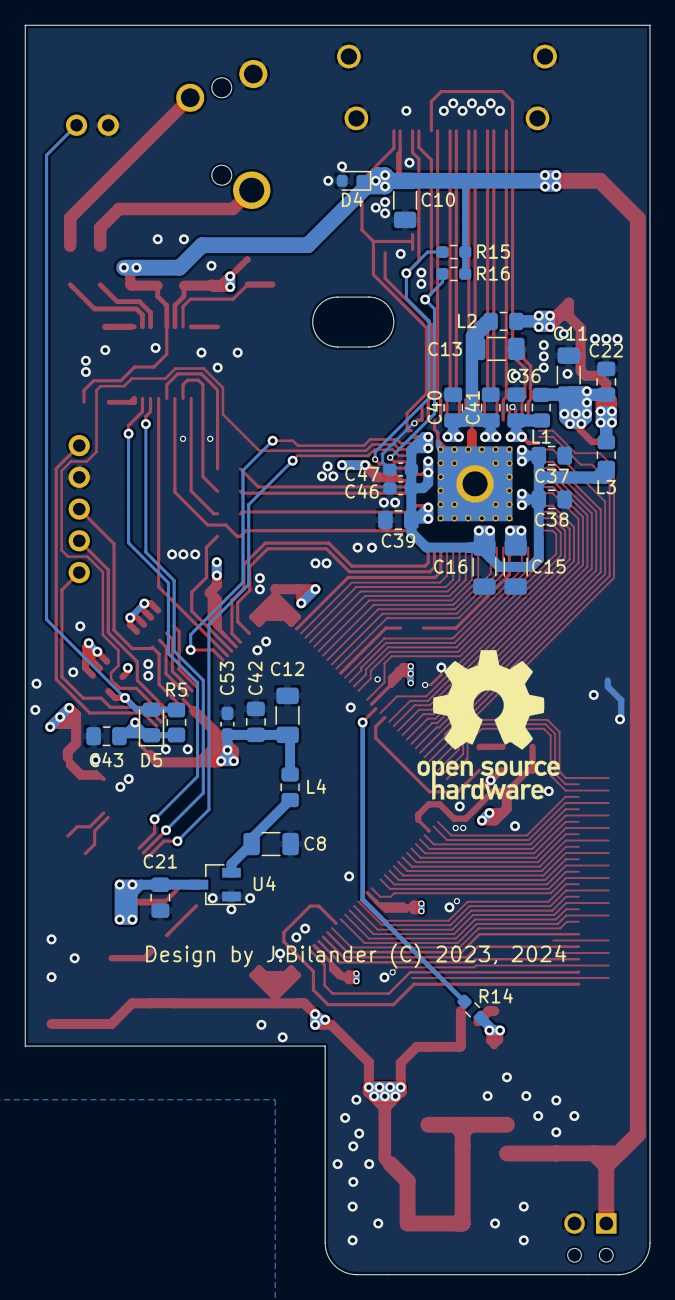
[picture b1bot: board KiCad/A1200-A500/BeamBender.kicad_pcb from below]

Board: 4 copper layers, 50.0 x 100.0 mm, 100 parts (31 on the bottom side), 122 nets.

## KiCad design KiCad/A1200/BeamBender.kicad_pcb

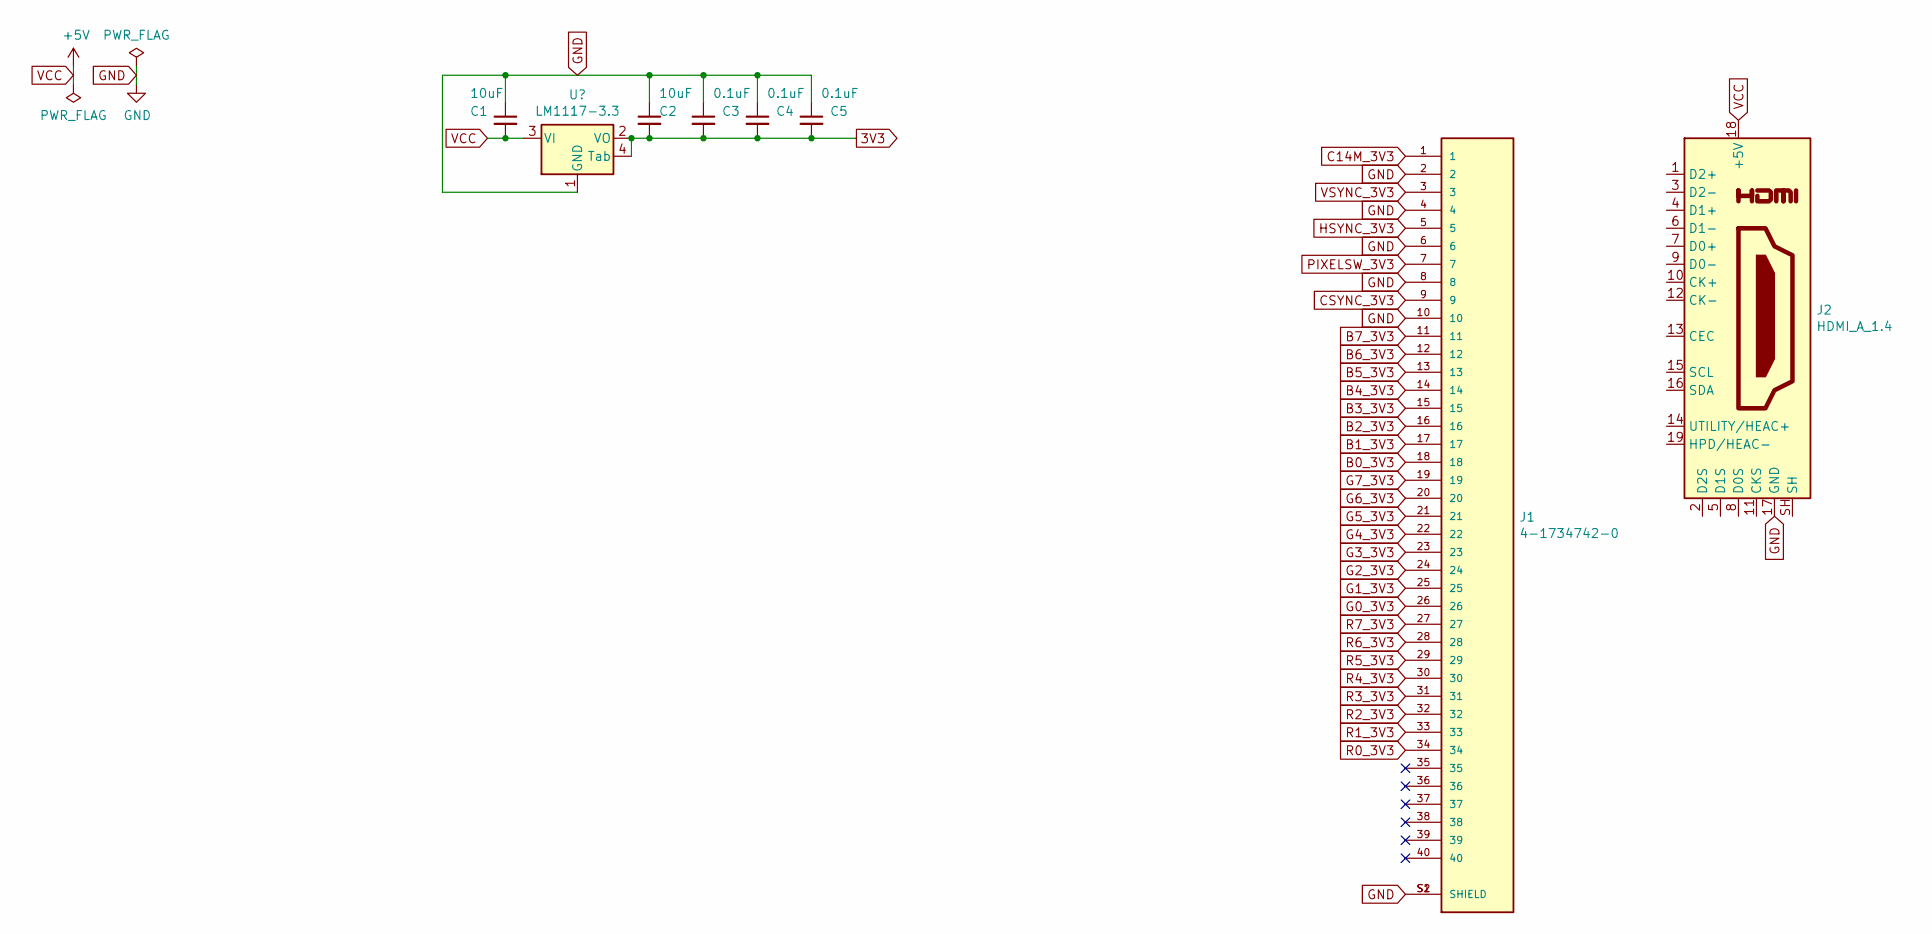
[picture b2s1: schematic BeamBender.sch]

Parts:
C1, C2: 10uF; C_1206_3216Metric_Pad1.42x1.75mm_HandSolder
C3, C4, C5: 0.1uF; C_0805_2012Metric_Pad1.15x1.40mm_HandSolder
J1: 4-1734742-0; TE_4-1734742-0; PARTREV P
J2: HDMI_A_1.4; HDMI-10029449-111RLF

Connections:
3V3: C2.2, C3.2, C4.2, C5.2; also elsewhere on the board
B0_3V3: J1.18
B1_3V3: J1.17
B2_3V3: J1.16
B3_3V3: J1.15
B4_3V3: J1.14
B5_3V3: J1.13
B6_3V3: J1.12
B7_3V3: J1.11
C14M_3V3: J1.1
CSYNC_3V3: J1.9
G0_3V3: J1.26
G1_3V3: J1.25
G2_3V3: J1.24
G3_3V3: J1.23
G4_3V3: J1.22
G5_3V3: J1.21
G6_3V3: J1.20
G7_3V3: J1.19
GND: C1.1, C2.1, C3.1, C4.1, C5.1, J1.2, J1.4, J1.6, J1.8, J1.10, J1.S1 (SHIELD), J1.S2 (SHIELD), J2.17 (GND); also elsewhere on the board
HSYNC_3V3: J1.5
PIXELSW_3V3: J1.7
R0_3V3: J1.34
R1_3V3: J1.33
R2_3V3: J1.32
R3_3V3: J1.31
R4_3V3: J1.30
R5_3V3: J1.29
R6_3V3: J1.28
R7_3V3: J1.27
VCC: C1.2, J2.18 (+5V); also elsewhere on the board
VSYNC_3V3: J1.3

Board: 2 copper layers, 8 parts (0 on the bottom side), 3 nets, no tracks yet.

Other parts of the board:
U1: LM1117-3.3; SOT-223

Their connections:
3V3: U1.2, U1.4; also elsewhere on the board
GND: U1.1; also elsewhere on the board
VCC: U1.3; also elsewhere on the board

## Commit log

2023-08-30 Create LICENSE
2023-09-19 Add KiCad footprints
2023-09-19 Added 3D-model
2023-09-19 Added KiCad files
2023-09-19 Renamed folder
2023-09-20 Added 3D-models
2023-09-20 Added footprint for 3.5mm audio input jack
2023-09-20 Added a 3.5mm input audio jack
2023-10-01 Adjusted hole in middle to dedicated A1200-design
2023-10-02 Moved mounting hole 1 mm up
2023-10-05 Added 3D-model of ADV7513 TQFP-64 package
2023-10-05 removed STX-3501-3N.lib
2023-10-05 Added ADV7513 HDMI-transmitter
2023-10-05 Added MSOP-10 footprint
2023-10-05 Added 3D-model of D5V0F4U10MR
2023-10-05 Added 4 channel low capacitance TVS diode array D5V0F4U10MR
2023-10-05 Added two more TVS-diodes for ESD-protection and started routing the diff-pairs
2023-10-06 Set default trace width to 6 mils
2023-10-06 more diff-pair routing
2023-10-06 more place and route
2023-10-07 Update file
2023-10-07 Added footprint
2023-10-07 Added a Phoenix Contact for +5V power supply and did some place and route around the 3.3V-regulator
2023-10-08 Added Polarized electrolytical capacitors for 3V3-power
2023-10-08 Fixed power place and route due to height constraint
2023-10-31 Added Gowin FPGA GW1NR-UV9LQ144P
2023-11-01 Added 27 MHz crystal oscillator X1 to GCLKT_4 pin and did some routing
2023-11-02 Changed to four layer stackup, added GND and 3V3 Power plane
2023-11-02 Changed to four layer stackup, added some caps and done some more routing
2023-11-02 more place and route done
2023-11-02 more place and route of pull-ups for SDL,SDA,DDC_SDL and DDC_SDA around ADV7513 chip
2023-11-02 more routing done
2023-11-03 Added Oscillator_7.0x5.0mm X2 on GCLKT_1 input and added damping resistor on PCLK
2023-11-08 Added a 1.8V LDO (MCP1702T-1802E_CB) in SOT-23 for powering the ADV7513 with 1.8V (DVDD,AVDD,PVDD,BGVDD)
2024-02-05 More power routing done
2024-02-07 More routing of power supply
2024-02-08 More 1.8V power routing and caps placement
2024-02-19 More power routing done for 1.8V to ADV7513
2024-02-20 more power routing
2024-02-20 Changed PD to pull-up instead of pull-down, fixed A1200 mounting hole and A500 cutout area
2024-02-20 Placement of C18,C19
2024-02-21 Breakout of own symbol for A500 drill-hole and more assignments of FPGA-pins
2024-02-21 Added 1k pull-down resistors on the FPGA's MODE0 and MODE1 pins
2024-02-21 Added JTAG-pinheader and pull-up resistor arrays
2024-02-23 Fixed JTAG-connector and remaining 3V3-power routing and pull-ups for FPGA
2024-02-24 Added RC-debounce circuit to Button 1 (BT1)
2024-02-25 Added ADC-chip AK5720VT
2024-02-26 added a 24.576 MHz crystal oscillator 5.0x3.2mm for Audio MCLK routed to FPGA pin 98 (GCLKT_2)
2024-02-26 Added series resistors to BCLK, LRCLK and I2S0 audio lines.
2024-02-27 Fixed the symbol for 3.5mm phono jack (STX-3501-3N) to be more clear with regards to TRS (Tip,Ring,Sleeve) pinout
2024-02-27 assigned the audio Left and Right channels to 3.5mm phono jack (STX-3501-3N) and to ADC-chip (AK5720)
2024-02-27 Added coupling caps for analogue left and right channel to inputs on ADC-chip (AK5720VT)
2024-02-27 Added a 0.47uF cap for ADC-chip VCOM pin (Voltage Reference)
2024-02-29 Repositioning of the AK5720 chip and routed the analog supply with 5V and digital supply with 3V3
2024-02-29 Added a pull-up resistor for GSEL (Gain-Select) input pin with a solder JP to be able to turn gain off = GND
2024-03-02 Finished routing the ak5720vt-chip, changed to a potential-divider for controlling GSEL-pin, PDN_RESET,FSEL and DIF-signals routed to spare pins in the FPGA
2024-03-05 Fixed assignment/enumeration of all capacitors from C1 to C54
2024-03-06 Some silkscreen text fixes and OSHW-logos placement done
2024-03-06 Fixed enumeration/order of all resistors on board and their reference placement on silkscreen
2024-03-06 Fixed ordering of L1-L4, changed R14-R21 to 33 Ohms, and swapped X2 and X3 reference
2024-03-07 Silkscreen fix
2024-03-07 Added screenshot 3D-images of first prototype
2024-03-07 small routing fix
2024-03-10 Add footprint
2024-03-10 Changed R12 to a selectable pull-up/pull-down three-pads footprint
2024-03-11 Added some GND via-stitching for the FPGA
2024-03-28 Added images
2024-04-23 modified .gitignore file
2024-04-23 Added .gitignore file
2024-04-23 Add fpga project base structure
2024-04-23 Add schematic pdf
2024-04-23 Add file
2024-04-23 modified file
2024-04-23 Add files
2024-04-24 deleted files
2024-04-24 Simplified example, derive the 25 MHz pixel clock from 50 MHz OSC
2024-05-27 Adapted design to take 1.8V on VCCIO3 because of embedded pSRAM requirement, changed RN1, RN2 to 4.7k Ohm, relocated pin FSEL and DIF/TDMI to bank0, moved PDN_RESET_N to pin 29 and MCLK to pin 30. JP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
2024-05-28 Added decoupling cap C55 (10nF 0603) to VCCIO3-input (DVDD)
2024-05-28 changed R12 from Resistor-jumper to pull-down only for PD-line
2024-07-22 Re-design with SiI9022A
2024-07-22 Updated file
2024-07-22 Add footprints
2024-07-22 Add 3D-models
2024-07-22 Moved the Phoenix-connector J4 and cap C17 a bit to the right
2024-07-23 Small improvement of routing VCC1V8 to VCCIO3-pins on the FPGA
2024-07-23 Added 3D-model of SP1003-01DTG TVS-Diode
2024-07-23 Added SP1003-01DTG TVS-Diode for ESD-protection of VCC-line
2024-07-28 Added silkscreen icons
2024-07-28 Fixed pin 1 indicator adding a dot on silkscreen
2024-07-29 Silkscreen fixes
2024-07-29 Placed net label for EXT_SWING
2024-09-07 small silkscreen and GND fix
2024-09-10 Add images of Rev. 1B
2024-09-10 fixed U-enumeration, changed U7 to U6
2024-09-19 fixed 480p example with sound working

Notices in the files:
KiCad/A1200-A500/BeamBender.kicad_pcb:
Design by J.Bilander (C) 2023, 2024
